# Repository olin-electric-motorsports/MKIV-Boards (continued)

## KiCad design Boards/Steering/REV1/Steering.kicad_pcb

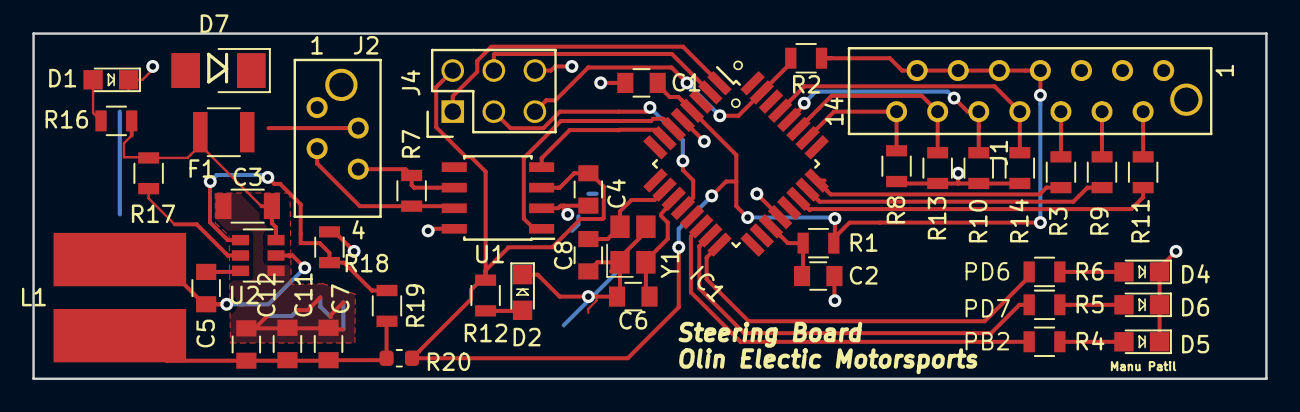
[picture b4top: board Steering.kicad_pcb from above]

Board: 2 copper layers, 76.2 x 21.3 mm, 44 parts (0 on the bottom side), 38 nets.

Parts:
C1, C4, C5, C12: C_0.1uF; C_0805_OEM
C2: C_100pF; C_0805_OEM
C3: C_22uF; C_1206_OEM
C6, C8: C_30pF; C_0805_OEM
C7: C_47uF; C_0805_OEM
C11: C_1uF; C_0805_OEM
D1, D2, D4, D5, D6: LED_0805; LED_0805_OEM
D7: D_Zener_18V; DO-214AA
F1: 500mA; Fuse_1210
IC1: ATMEGA16M1; TQFP-32_7x7mm_Pitch0.8mm
J1: MM_F_VT_14; micromatch_female_vert_14
J2: MM_F_VT_04; micromatch_female_vert_4
J4: CONN_02X03; Pin_Header_Straight_2x03
L1: L_4.7uH; 4.7uH_Inductor_OEM
R1: R_100; R_0805_OEM
R2, R17, R18: R_10K; R_0805_OEM
R3, R4, R5, R6, R7, R9, R11, R12: R_200; R_0805_OEM
R8, R10, R13, R14: R_1M; R_0805_OEM
R16: R_1K; R_0805_OEM
R19: R_51.1K; R_0805_OEM
R20: R_0; R_0603_1608Metric
U1: MCP2561-E_SN; SOIC-8_3.9x4.9mm_Pitch1.27mm_OEM
U2: TPS561201; SOT-23-6_OEM
Y1: Crystal_SMD; Crystal_SMD_FA238

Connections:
+12V: D7.1, F1.1, J2.2
/12V_Fused: C3.1, F1.2, R16.1, R17.2, U2.3
/B1_In: IC1.26, J1.14, R8.1
/B2_In: IC1.27, J1.12, R13.1
/B3_In: IC1.28, J1.10, R10.1
/B4_In: IC1.29, J1.8, R14.1
/CANH: J2.3, R7.1, U1.7
/CANL: J2.4, R7.2, U1.6
/LED1_Out: J1.6, R3.1
/LED2_Out: J1.4, R9.1
/LED3_Out: J1.2, R11.1
/LED_Driver1: IC1.24, R3.2
/LED_Driver2: IC1.23, R9.2
/LED_Driver3: IC1.22, R11.2
/MISO: IC1.1, J4.1
/MOSI: IC1.2, J4.4
/P_LED_1: IC1.14, R4.1
/P_LED_2: IC1.15, R5.1
/P_LED_3: IC1.16, R6.1
/RESET: IC1.31, J4.5, R2.2
/RXCAN: IC1.7, U1.4
/SCK: IC1.12, J4.3
/TXCAN: IC1.6, U1.1
GND: C1.2, C2.2, C3.2, C4.2, C6.2, C7.2, C8.2, C11.2, C12.2, D1.1, D2.1, D4.1, D5.1, D6.1, D7.2, IC1.5, IC1.20, J1.1, J1.3, J1.5, J2.1, J4.6, R8.2, R10.2, R13.2, R14.2, R18.2, U1.2, U1.8, U2.1, Y1.2, Y1.4
unnamed: C2.1, IC1.19, R1.2
unnamed: C5.1, U2.6
unnamed: C5.2, L1.1, U2.2
unnamed: C6.1, IC1.11, Y1.1
unnamed: C8.1, IC1.10, Y1.3
unnamed: C7.1, C11.1, C12.1, L1.2, R19.1, R20.2
unnamed: D1.2, R16.2
unnamed: D2.2, R12.2
unnamed: D4.2, R6.2
unnamed: D5.2, R4.2
unnamed: D6.2, R5.2
unnamed: R17.1, U2.5
unnamed: R18.1, R19.2, U2.4
VCC: C1.1, C4.1, IC1.4, J1.7, J1.9, J1.11, J1.13, J4.2, R1.1, R2.1, R12.1, R20.1, U1.3

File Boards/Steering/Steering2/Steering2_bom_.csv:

Component,Description,Part,References,Value,Footprint,Quantity Per PCB,Datasheet,Package,MPN,MFN,PurchasingLink
1,"Capacitor, 0.1uF, 50V, 5%, 0805",C_0.1uF,C1 C4 C5 C9 C10 C12,C_0.1uF,C_0805_OEM,6,http://datasheets.avx.com/X7RDielectric.pdf,Value,478-3352-1-ND,DigiKey,https://www.digikey.com/products/en?keywords=478-3352-1-ND
2,"Capacitor, 100pF, 50V, 5%, 0805",C_100pF,C2,C_100pF,C_0805_OEM,1,https://content.kemet.com/datasheets/KEM_C1003_C0G_SMD.pdf,Value,399-1122-1-ND,DigiKey,https://www.digikey.com/product-detail/en/kemet/C0805C101J5G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
3,"Capacitor, 1uF, 25V, 10%, 0805",C_1uF,C11,C_1uF,C_0805_OEM,1,http://datasheets.avx.com/X7RDielectric.pdf,Value,478-10487-1-ND,DigiKey,https://www.digikey.com/product-detail/en/avx-corporation/08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
4,"Capacitor, 22uF, 16V, 20%, 1206",C_22uF,C3,C_22uF,C_1206_OEM,1,http://www.samsungsem.com/kr/support/product-search/mlcc/__i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,Value,1276-2725-1-ND,DigiKey,https://www.digikey.com/products/en?keywords=1276-2725-1-ND
5,"Capacitor, 30pF, 50V, 5%, 0805",C_30pF,C6 C8,C_30pF,C_0805_OEM,2,https://media.digikey.com/pdf/Data%20Sheets/Samsung%20PDFs/C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,Value,1276-1130-1-ND,DigiKey,https://www.digikey.com/product-detail/en/samsung-electro-me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
6,"Capacitor, 47uF, 6.3V, 20%, 0805",C_47uF,C7,C_47uF,C_0805_OEM,1,http://www.yuden.co.jp/productdata/catalog/en/mlcc_all_e.pdf,Value,587-4280-1-ND,DigiKey,https://www.digikey.com/product-detail/en/taiyo-yuden/JMK212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
7,"Diode, Zener, 18V, 5W, 5%",D_Zener_18V,D7,D_Zener_18V,DO-214AA,1,http://www.mccsemi.com/up_pdf/SMBJ5338B-SMBJ5388B(SMB).pdf,DO-214AA (SMB),SMBJ5355B-TPMSCT-ND,DigiKey,https://www.digikey.com/products/en?keywords=SMBJ5355B-TPMSCT-ND
8,"LED, Green, 2.2V, 20mA, 0805",LED_0805,D1 D2 D4 D5 D6,LED_0805,LED_0805_OEM,5,http://www.osram-os.com/Graphics/XPic9/00078860_0.pdf,Value,475-1410-1-ND,DigiKey,https://www.digikey.com/products/en?keywords=475-1410-1-ND
9,"Fuse, PTC, 500mA, 16V, 1210",F_500mA_16V,F1,500mA,Fuse_1210,1,https://belfuse.com/resources/CircuitProtection/datasheets/0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,Value,507-1786-1-ND,DigiKey,https://www.digikey.com/product-detail/en/bel-fuse-inc/0ZCH0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
10,"Microcontroller, 8-bit, 1KB RAM, 16KB Flash",ATMEGA16M1,IC1,ATMEGA16M1,TQFP-32_7x7mm_Pitch0.8mm,1,http://www.atmel.com/Images/Atmel-8209-8-bit%20AVR%20ATmega1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,Value,ATMEGA16M1-AU-ND,DigiKey,https://www.digikey.com/product-detail/en/atmel/ATMEGA16M1-A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
11,"Connector header through hole 2x3 0.100"" (2.54mm)",CONN_02X03,J4,CONN_02X03,Pin_Header_Straight_2x03,1,http://portal.fciconnect.com/Comergent//fci/drawing/67996.pdf,Value,609-3234-ND,DigiKey,https://www.digikey.com/product-detail/en/amphenol-fci/67997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
12,NanoFit Female Right Angle 2x02,NF_F_RA_2x02,J3,NF_F_RA_2x02,Molex_Nano-Fit_105314-xx04_2x02_P2.50mm_Horizontal,1,https://www.molex.com/pdm_docs/sd/1053141104_sd.pdf,,WM14976-ND ,DigiKey,https://www.digikey.com/product-detail/en/molex-llc/10531412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
13,NanoFit Female Right Angle 2x03,NF_F_RA_2x03,J1,NF_F_RA_2x03,Molex_Nano-Fit_105314-xx06_2x03_P2.50mm_Horizontal,1,https://www.molex.com/pdm_docs/sd/1053141106_sd.pdf,,WM14977-ND ,DigiKey,https://www.digikey.com/product-detail/en/molex-llc/10531412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
14,NanoFit Female Right Angle 2x04,NF_F_RA_2x04,J2,NF_F_RA_2x04,Molex_Nano-Fit_105314-xx08_2x04_P2.50mm_Horizontal,1,https://www.molex.com/pdm_docs/sd/1053141108_sd.pdf,,WM14978-ND ,DigiKey,https://www.digikey.com/product-detail/en/molex-llc/10531412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
15,"Inductor, 4.7uH, 4.4A, 25mOhm, 20%",L_4.7uH,L1,L_4.7uH,4.7uH_Inductor_OEM,1,https://product.tdk.com/info/en/documents/wdcatalog/withdraw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,Value,445-6583-1-ND,DigiKey,https://www.digikey.com/product-detail/en/tdk-corporation/VL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
16,"Resistor, 0 ohm jumper, 0.1W, 0603",R_0,R20,R_0,R_0603_1608Metric,1,http://industrial.panasonic.com/www-cgi/jvcr13pz.cgi?E+PZ+3+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,,P0.0GCT-ND,DigiKey,https://www.digikey.com/product-detail/en/panasonic-electron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
17,"Resistor, 100, 0.25W, 1%, 0805",R_100,R1,R_100,R_0805_OEM,1,https://www.seielect.com/Catalog/SEI-rncp.pdf,Value,RNCP0805FTD100RCT-ND,DigiKey,https://www.digikey.com/products/en?keywords=RNCP0805FTD100RCT-ND
18,"Resistor, 10K, 0.25W, 1%, 0805",R_10K,R2 R17 R18,R_10K,R_0805_OEM,3,http://www.bourns.com/data/global/pdfs/CRS.pdf,,CRS0805-FX-1002ELFCT-ND,DigiKey,https://www.digikey.com/products/en?keywords=CRS0805-FX-1002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
19,"Resistor, 1K, 0.25W, 1%, 0805",R_1K,R16,R_1K,R_0805_OEM,1,https://www.seielect.com/Catalog/SEI-rncp.pdf,,RNCP0805FTD1K00CT-ND,DigiKey,https://www.digikey.com/products/en?keywords=RNCP0805FTD1K00CT-ND
20,NanoFit Female Right Angle 2x02,R_1M,R8 R10 R13 R14,R_1M,R_0805_OEM,4,https://www.seielect.com/Catalog/SEI-rncp.pdf,,RMCF0805JT1M00CT-ND,DigiKey,https://www.digikey.com/product-detail/en/stackpole-electron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
21,"Resistor, 200, 0.125W, 5%, 0805",R_200,R3 R4 R5 R6 R7 R9 R11 R12,R_200,R_0805_OEM,8,https://www.seielect.com/Catalog/SEI-RMCF_RMCP.pdf,Value,RMCF0805JT200RCT-ND,DigiKey,https://www.digikey.com/products/en?keywords=RMCF0805JT200RCT-ND
22,"Resistor, 51.1K, 0.125W, 1%, 0805",R_51.1K,R19,R_51.1K,R_0805_OEM,1,https://industrial.panasonic.com/cdbs/www-data/pdf/RDA0000/A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,,P51.1KCCT-ND,DigiKey,https://www.digikey.com/product-detail/en/panasonic-electron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
23,"Linear regulator, 30V max input, 3.3V output, 100mA",LM3480,U3,LM3480,SOT-23-3-Lead_TabPin2,1,http://www.ti.com/lit/ds/symlink/lm3480.pdf,,LM3480IM3-3.3CT-ND,DigiKey,https://www.digikey.com/product-detail/en/texas-instruments/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
24,"High speed CAN transceiver, 1Mb/s",MCP2561-E_SN,U1,MCP2561-E_SN,SOIC-8_3.9x4.9mm_Pitch1.27mm_OEM,1,http://www.microchip.com/mymicrochip/filehandler.aspx?ddocna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,,MCP2561-E/SN-ND,DigiKey,https://www.digikey.com/products/en?keywords=mcp2561-e%2Fsn
25,"Buck converter, 4.5-17V input, adj 0.76-7V output, 1A, 580kHz",TPS561201,U2,TPS561201,SOT-23-6_OEM,1,http://www.ti.com/lit/ds/symlink/tps561201.pdf,Value,TPS561201,DigiKey,https://www.digikey.com/products/en?keywords=296-46928-1-ND
26,CRYSTAL 16.0000MHZ 18PF SMD,Crystal_SMD,Y1,Crystal_SMD,Crystal_SMD_FA238,1,https://support.epson.biz/td/api/doc_check.php?dl=brief_FA-2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,Value,SER3686CT-ND,DigiKey,https://www.digikey.com/products/en?keywords=SER3686CT-ND
,,,,,,,,,,,
,,,,,,,,,,,
,,,,,,,,,,,
,,,,,,,,,,,
,,,,,,,,,,,
Component Groups:,26,,,,,,,,,,
Component Count:,48,,,,,,,,,,
Fitted Components:,48,,,,,,,,,,
Number of PCBs:,1,,,,,,,,,,
Total components:,48,,,,,,,,,,
Schematic Version:,,,,,,,,,,,
Schematic Date:,,,,,,,,,,,
BoM Date:,Wed 05 Dec 2018 09:20:35 PM EST,,,,,,,,,,
Schematic Source:,/home/manu/Desktop/Formula/MKIV-Boards/Boards/Steering/Steering2/Steering2.sch,,,,,,,,,,
KiCad Version:,Eeschema 5.0.0-fee4fd1~66~ubuntu18.04.1,,,,,,,,,,

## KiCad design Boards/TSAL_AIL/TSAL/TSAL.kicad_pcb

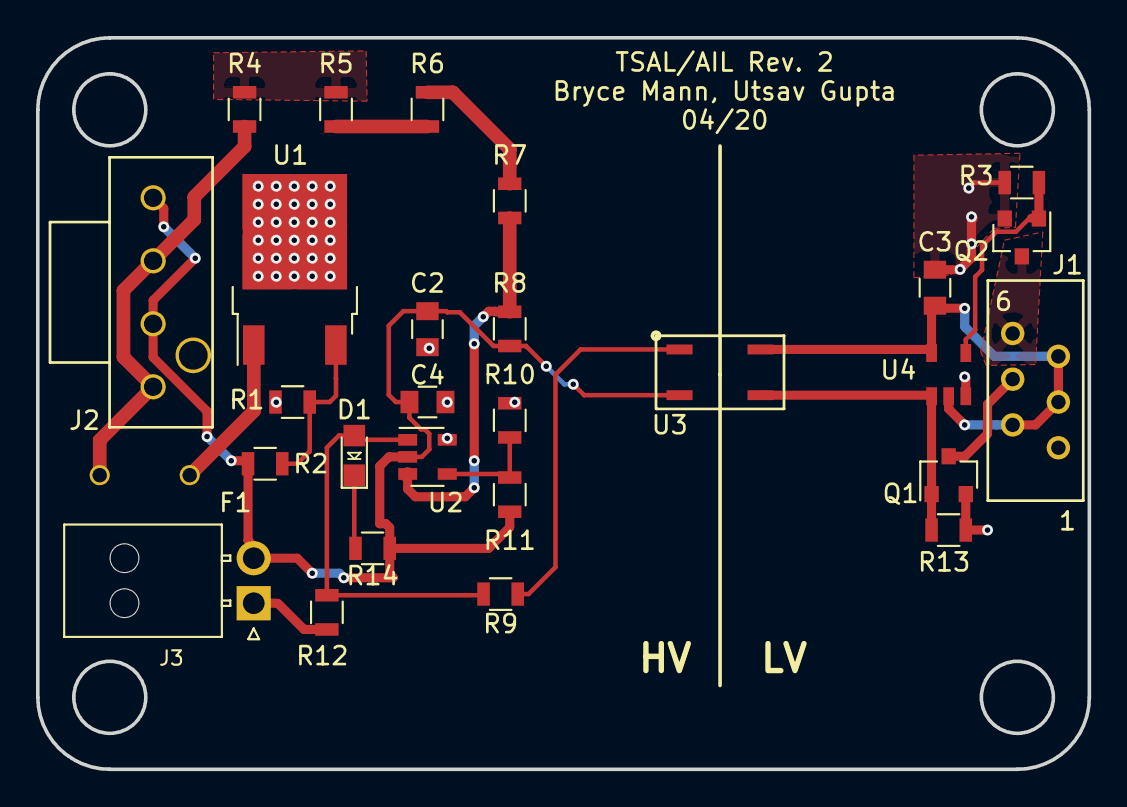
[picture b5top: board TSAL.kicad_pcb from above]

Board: 2 copper layers, 58.4 x 40.6 mm, 28 parts (0 on the bottom side), 20 nets.

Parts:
C2: C_10uF; C_0805_OEM
C3: C_1uF; C_0805_OEM
C4: C_0.1uF; C_0805_OEM
D1: LED_0805; LED_0805_OEM
F1: F_21mA_420V
J1: MM_F_RA_06; micromatch_female_ra_6
J2: Ultrafit_4_RA; Ultrafit_4
J3: NanoFit_2; NanoFit_Molex_1x02x2.50mm_Angled_OEM
Q1, Q2: SSM3K333R; SOT-23F
R1, R10, R14: R_1K; R_0805_OEM
R2: R_3K; R_0805_OEM
R3, R8, R13: R_10K; R_0805_OEM
R4, R5, R6: R_270K; R_0805_OEM
R7: R_178K; R_0805_OEM
R9: R_499; R_0805_OEM
R11: R_137; R_0805_OEM
R12: R_1.43K; R_0805_OEM
U1: LR8K4-G; TO-252-2
U2: MCP6001; SOT-23-5_OEM
U3: CPC1025NTR; 4-pin_SOP
U4: BU4S11G2-TR; SSOP5

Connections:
/5V: C2.2, C4.2, R1.1, R10.2, U1.2, U2.5
/AIL+: J3.1, R12.2
/AIL-: C2.1, C4.1, J2.2, J2.4, J3.2, R2.2, R8.2, R11.2, R14.2, U2.2, U3.2
/GLV+: C3.2, J1.2, J1.3, J1.5, U3.4, U4.2, U4.5
/TS+: F1.2, J2.1, J2.3, R4.2
/TSAL_FLAG: Q1.1, R13.1, U3.3, U4.1
/TSAL_GREEN-: J1.6, Q2.3
/TSAL_RED-: J1.4, Q1.3
GND: C3.1, J1.1, Q1.2, Q2.2, R3.2, R13.2, U4.3
unnamed: D1.1, R14.1
unnamed: D1.2, R9.2, R12.1, U2.1
unnamed: F1.1, U1.1
unnamed: Q2.1, R3.1, U4.4
unnamed: R1.2, R2.1, U1.3
unnamed: R4.1, R5.2
unnamed: R5.1, R6.2
unnamed: R6.1, R7.2
unnamed: R7.1, R8.1, U2.3
unnamed: R9.1, U3.1
unnamed: R10.1, R11.1, U2.4
